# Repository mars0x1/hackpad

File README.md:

# Mars Hackpad 🚀

Mars Hackpad is a 12-input productivity tool designed for seamless media control and custom shortcuts. It features an 11-key matrix and a rotary encoder, providing a tactical way to manage your workspace. It is powered by the **Seeed XIAO RP2040** and runs on **KMK firmware**.

## Features
* **128x64 OLED Display**: Provides real-time status updates via I2C (SDA: D4, SCL: D5).
* **EC11 Rotary Encoder**: Mapped to system volume control. Press the encoder to toggle **System Mute**.
* **11 Mechanical Keys**: Currently configured with macros for **Undo**, **Copy**, **Paste**, and a dedicated **Mic Mute** shortcut (FN + F5).
* **3D Printed Case**: A two-piece snap-fit design that holds the PCB and display at an ergonomic angle.

## CAD Model

* The case was designed in Fusion360 . 
* It consists of two printed parts: a **Top Case** with cutouts for the keys and screen, and a **Bottom Case** to protect the electronics.
* Everything is held together by M3 bolts.

## PCB
My PCB was designed in KiCad. It features a 4x3 matrix layout and custom silkscreen labeling.
* **Schematic**:
*  

* **PCB Layout**:
* 

* I used standard MX-style footprints for the keys and ensured the XIAO RP2040 sits centrally for easy USB-C access.

## Firmware Overview
This hackpad uses **KMK Firmware** (CircuitPython).
* **Matrix Setup**: Rows use pins **D0, D1, D2, D3** and Columns use **D6, D7, D9**.
* **Rotary Encoder**: Mapped to pins **D11** and **D10**.
* **Shortcuts**: The firmware is set up to handle common productivity commands without needing to touch the main keyboard.

## BOM (Bill of Materials)
Here is everything you need to build the Mars Hackpad:

| Item | Quantity | Description |
| :--- | :--- | :--- |
| **Seeed XIAO RP2040** | 1 | Main Microcontroller |
| **0.91 inch OLED display** | 1 | I2C Display |
| **EC11 Encoder** | 1 | Rotary Encoder with push-button |
| **MX Switches** | 11 | Your choice of mechanical switches |
| **1N4148 Diodes** | 12 | Switching Diodes for the matrix |
| **Case** | 2 parts | 3D Printed Top and Bottom shells |
| **M3 Bolts** | 4 | To secure the case halves |

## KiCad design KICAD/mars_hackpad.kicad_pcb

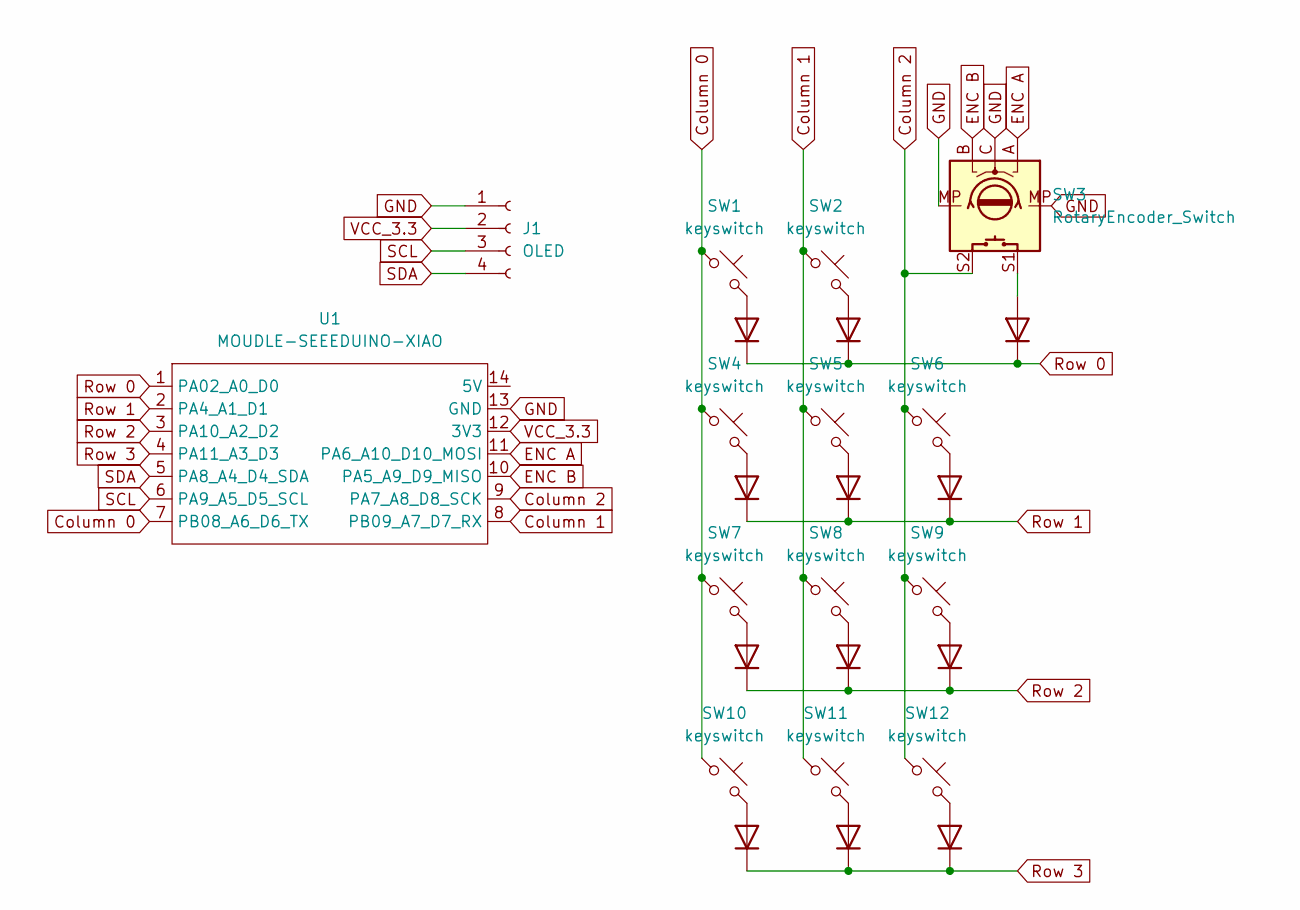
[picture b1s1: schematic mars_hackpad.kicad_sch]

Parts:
D1, D2, D3, D4, D5, D6, D7, D8, D9, D10, D11, D12: 1N4148; D_DO-35_SOD27_P7.62mm_Horizontal
J1: OLED; SSD1306-0.91-OLED-4pin-128x32
SW1, SW2, SW4, SW5, SW6, SW7, SW8, SW9, SW10, SW11, SW12: keyswitch; SW_Cherry_MX_1.00u_PCB1
SW3: RotaryEncoder_Switch; RotaryEncoder_Alps_EC11E-Switch_Vertical_H20mm
U1: MOUDLE-SEEEDUINO-XIAO; XIAO-Generic-Hybrid-14P-2.54-21X17.8MM

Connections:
Column 0: SW1.1, SW4.1, SW7.1, SW10.1, U1.7 (PB08_A6_D6_TX)
Column 1: SW2.1, SW5.1, SW8.1, SW11.1, U1.8 (PB09_A7_D7_RX)
Column 2: SW3.S2, SW6.1, SW9.1, SW12.1, U1.9 (PA7_A8_D8_SCK)
ENC A: SW3.A, U1.11 (PA6_A10_D10_MOSI)
ENC B: SW3.B, U1.10 (PA5_A9_D9_MISO)
GND: J1.1, SW3.C, SW3.MP, U1.13 (GND)
unnamed: D1.2 (A), SW1.2
unnamed: D2.2 (A), SW2.2
unnamed: D3.2 (A), SW3.S1
unnamed: D4.2 (A), SW4.2
unnamed: D5.2 (A), SW5.2
unnamed: D6.2 (A), SW6.2
unnamed: D7.2 (A), SW7.2
unnamed: D8.2 (A), SW8.2
unnamed: D9.2 (A), SW9.2
unnamed: D10.2 (A), SW10.2
unnamed: D11.2 (A), SW11.2
unnamed: D12.2 (A), SW12.2
Row 0: D1.1 (K), D2.1 (K), D3.1 (K), U1.1 (PA02_A0_D0)
Row 1: D4.1 (K), D5.1 (K), D6.1 (K), U1.2 (PA4_A1_D1)
Row 2: D7.1 (K), D8.1 (K), D9.1 (K), U1.3 (PA10_A2_D2)
Row 3: D10.1 (K), D11.1 (K), D12.1 (K), U1.4 (PA11_A3_D3)
SCL: J1.3, U1.6 (PA9_A5_D5_SCL)
SDA: J1.4, U1.5 (PA8_A4_D4_SDA)
VCC_3.3: J1.2, U1.12 (3V3)

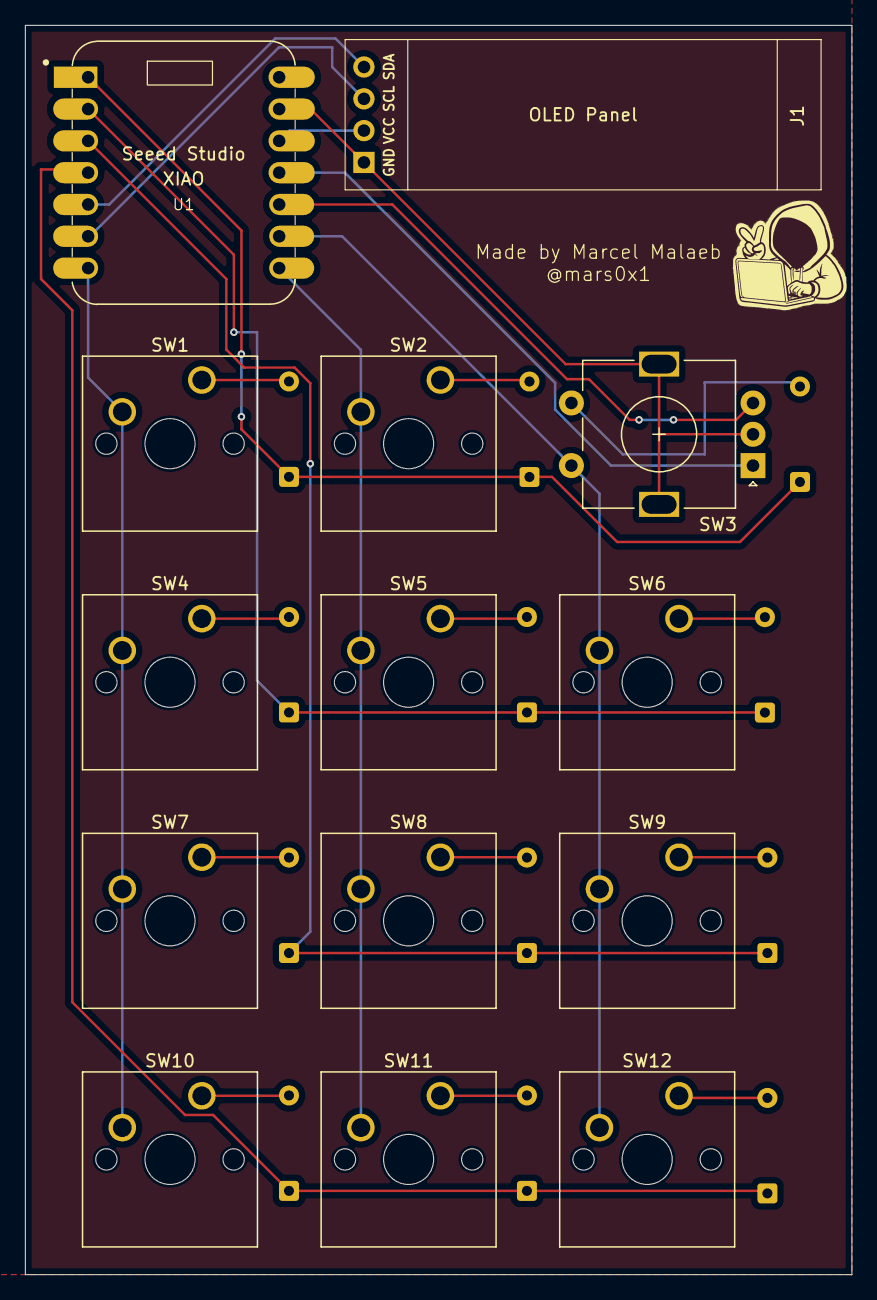
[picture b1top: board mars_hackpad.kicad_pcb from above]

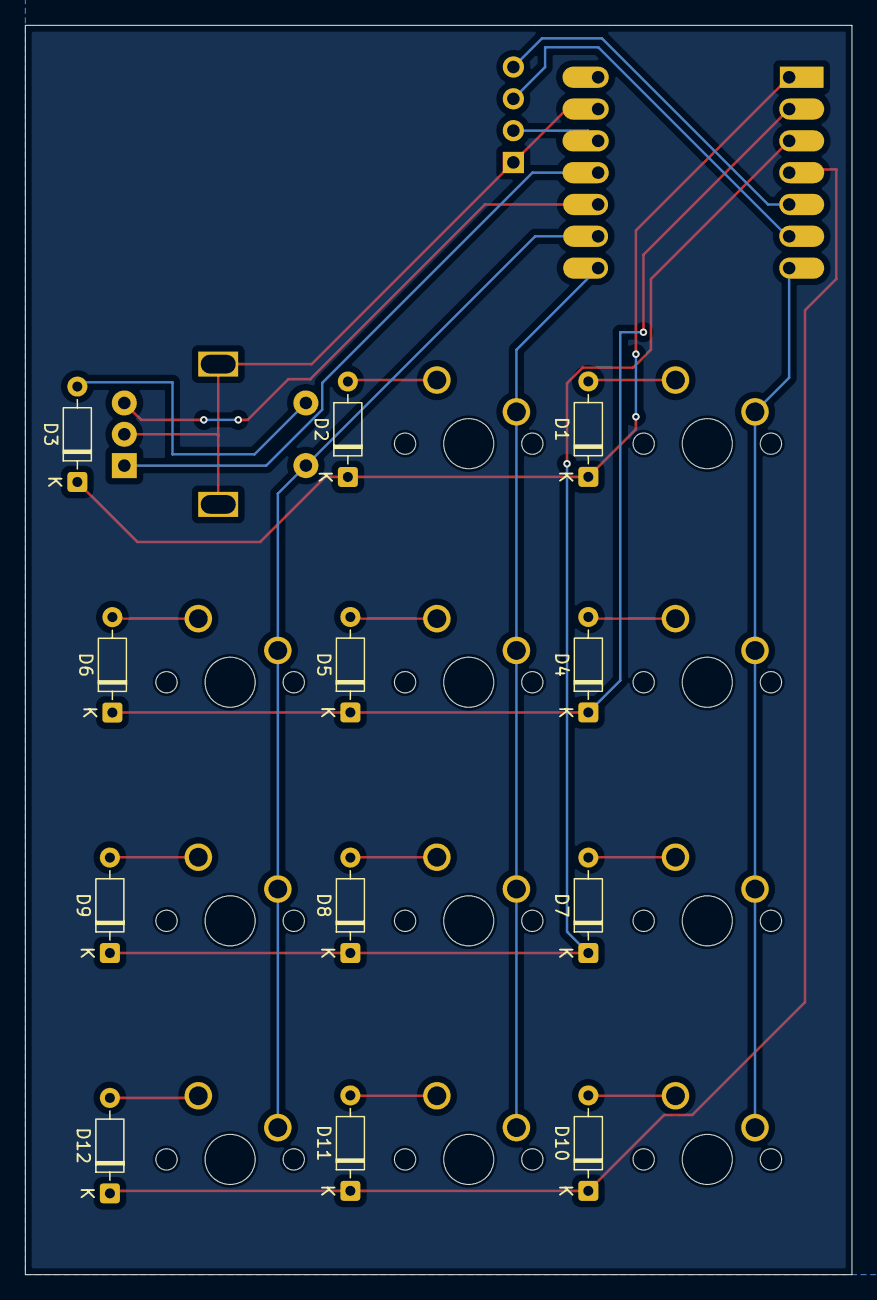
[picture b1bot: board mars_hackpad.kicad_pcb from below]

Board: 2 copper layers, 66.0 x 99.8 mm, 26 parts (12 on the bottom side), 25 nets.

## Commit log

2026-02-13 Initial upload of pcb project folders
2026-02-15 Add firmware overview section to README
2026-02-16 fixed the files
